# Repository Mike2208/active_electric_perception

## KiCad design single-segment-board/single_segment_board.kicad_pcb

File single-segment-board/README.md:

# single-segment-board

Board for processing single capacitive sensor segment

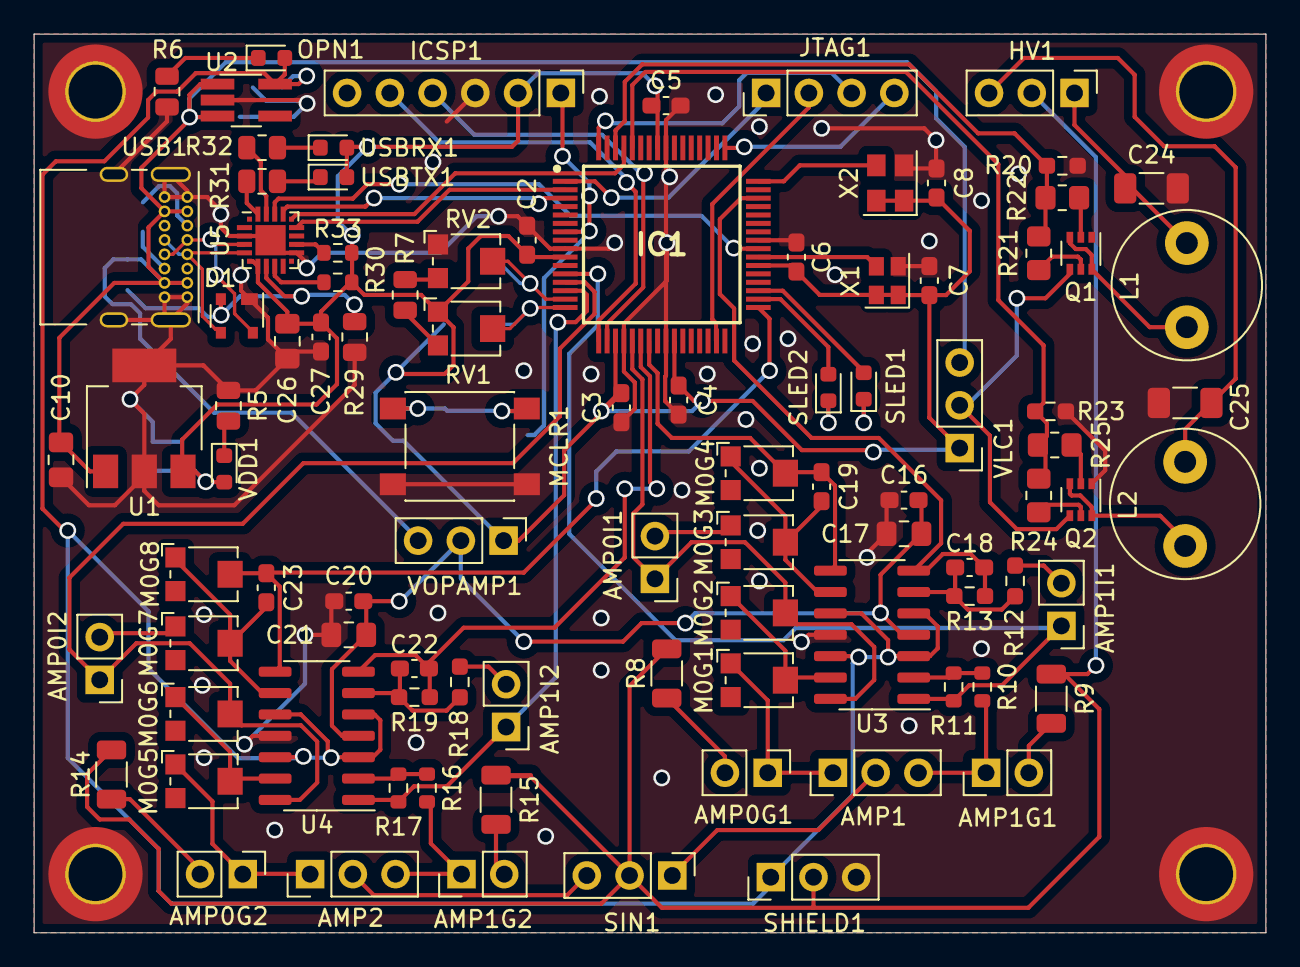
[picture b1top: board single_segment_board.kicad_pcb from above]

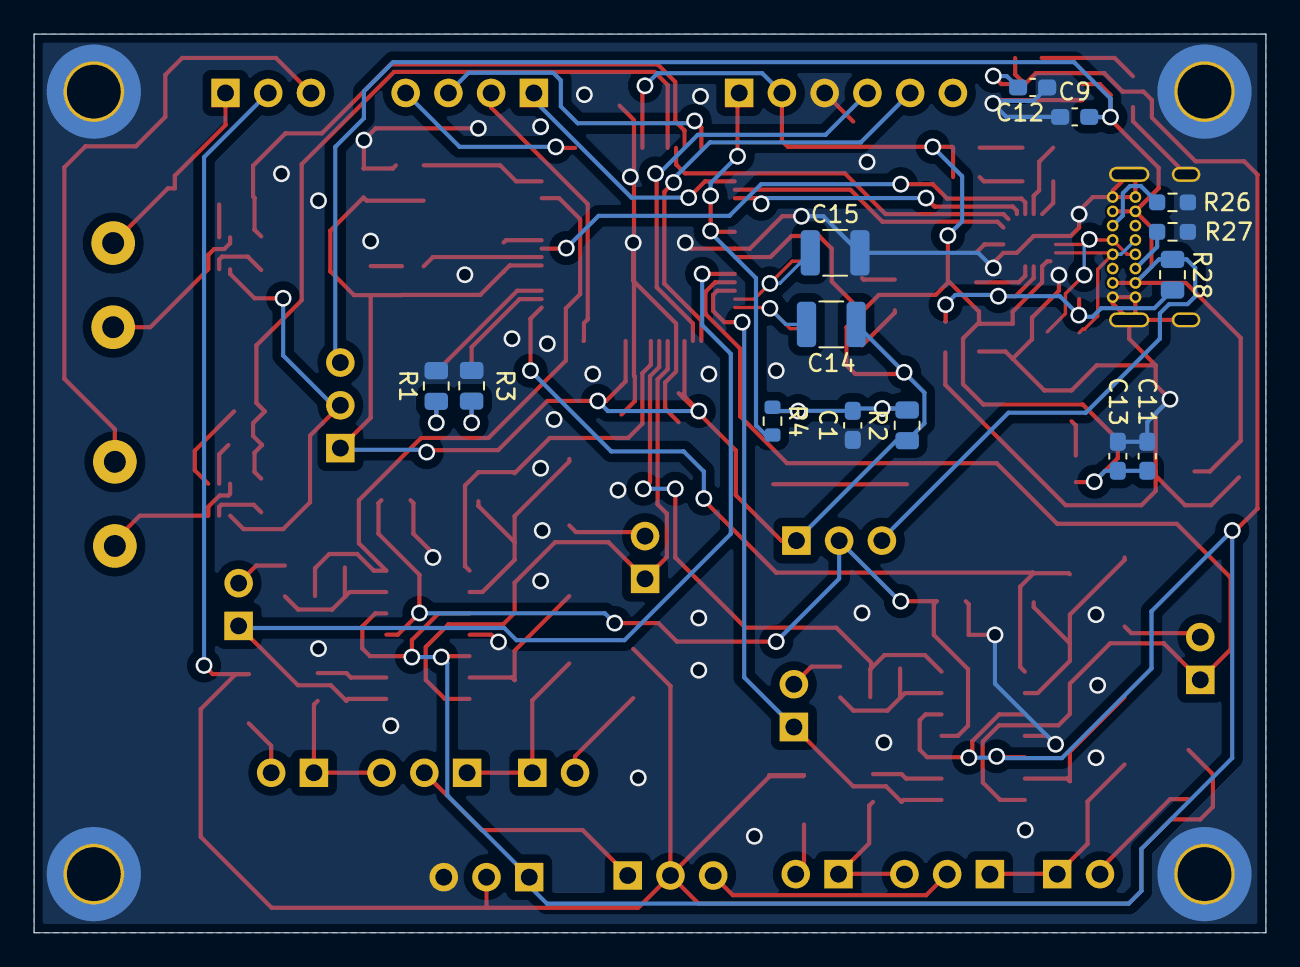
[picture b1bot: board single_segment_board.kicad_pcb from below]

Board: 2 copper layers, 73.2 x 53.4 mm, 112 parts (14 on the bottom side), 82 nets.

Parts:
AMP0G1, AMP0G2, AMP0I1, AMP0I2, AMP1G1, AMP1G2, AMP1I1, AMP1I2: Jumper_2_Open; PinHeader_1x02_P2.54mm_Vertical
AMP1, AMP2: Jumper_3_Bridged12; PinHeader_1x03_P2.54mm_Vertical
C1, C2, C3, C4, C5, C6, C7, C8, C13, C27: 0.1u; C_0603_1608Metric_Pad1.08x0.95mm_HandSolder
C9, C11, C12: 1u; C_0603_1608Metric_Pad1.08x0.95mm_HandSolder
C10, C26: 4.7u; C_0805_2012Metric_Pad1.18x1.45mm_HandSolder
C14, C15: 0.1u; C_1210_3225Metric
C16, C20: .01uF; C_0603_1608Metric_Pad1.08x0.95mm_HandSolder
C17, C21: 10uF; C_0805_2012Metric_Pad1.18x1.45mm_HandSolder
C18, C19, C22, C23: 10p; C_0603_1608Metric_Pad1.08x0.95mm_HandSolder
C24, C25: 47pF; C_1206_3216Metric_Pad1.33x1.80mm_HandSolder
D1: SP0503BAHT; SOT-143
H1, H2, H3, H4: MountingHole_Pad; MountingHole_3.2mm_M3_DIN965_Pad_TopBottom
HV1: Conn_01x03; PinHeader_1x03_P2.54mm_Vertical
IC1: PIC32MK0512MCJ064-I_PT; QFP50P1200X1200X120-64N
ICSP1: ICSP; PinHeader_1x06_P2.54mm_Vertical
JTAG1: JTAG; PinHeader_1x04_P2.54mm_Vertical
L1, L2: 47mH; L_Radial_D8.7mm_P5.00mm_Fastron_07HCP
M0G1, M0G2, M0G3, M0G4, M0G5, M0G6, M0G7, M0G8: RP_500k; Potentiometer_Bourns_TC33X_Vertical
MCLR1: SW_MEC_5E; SW_SPST_PTS645
OPN1: GLED; LED_0603_1608Metric
Q1, Q2: MBT3946DW1T1; SOT-363_SC-70-6
R1, R3, R5, R31, R32: 330; R_0805_2012Metric
R2: 10k; R_0805_2012Metric
R4, R30, R33: 1k; R_0603_1608Metric
R6: 165; R_0805_2012Metric
R7: 150k; R_0805_2012Metric
R8, R9, R14, R15: 1meg; R_1206_3216Metric
R10, R11, R16, R17: 10k; R_0603_1608Metric
R12, R13, R18, R19: 1k; R_0603_1608Metric_Pad0.98x0.95mm_HandSolder
R20, R23: 100k; R_0603_1608Metric_Pad0.98x0.95mm_HandSolder
R21, R22, R24, R25: 10k; R_0805_2012Metric_Pad1.20x1.40mm_HandSolder
R26, R27: 5.1k; R_0603_1608Metric_Pad0.98x0.95mm_HandSolder
R28: 22.1k; R_0805_2012Metric
R29: 47.5k; R_0805_2012Metric
RV1, RV2: RP_50k; Potentiometer_Bourns_TC33X_Vertical
SHIELD1: Jumper_3_Bridged12; PinHeader_1x03_P2.54mm_Vertical
SIN1: Conn_01x03; PinHeader_1x03_P2.54mm_Vertical
SLED1: GLED; LED_0603_1608Metric
SLED2: RLED; LED_0603_1608Metric
U1: MCP1826S; SOT-223-3_TabPin2
U2: NCV8114ASN165T1G; TSOT-23-5_HandSoldering
U3, U4: ADA4891-4; SOIC-14_3.9x8.7mm_P1.27mm
U5: CP2102N-Axx-xQFN20; SiliconLabs_QFN-20-1EP_3x3mm_P0.5mm_EP1.8x1.8mm
USB1: USB_C_Receptacle_USB2.0; USB_C_Receptacle_GCT_USB4085
USBRX1: RLED; LED_0603_1608Metric
USBTX1: GLED; LED_0603_1608Metric
VDD1: GLED; LED_0603_1608Metric
VLC1: Jumper_3_Bridged12; PinHeader_1x03_P2.54mm_Vertical
VOPAMP1: Jumper_3_Bridged12; PinHeader_1x03_P2.54mm_Vertical
X1: SG-210STF; Oscillator_SMD_SeikoEpson_SG210-4Pin_2.5x2.0mm
X2: ECS-327MVATX-3-CN-TR; Oscillator_SMD_Abracon_ASE-4Pin_3.2x2.5mm

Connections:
+3V3: C2.2, C3.1, C4.2, C5.2, C6.1, C7.1, C8.1, C11.1, C13.1, C14.1, C26.1, C27.1, IC1.10 (VDD_1), IC1.19 (AVDD), IC1.26 (VDD_2), IC1.38 (VDD_3), IC1.57 (VDD_4), ICSP1.2, R2.2, R30.2, R33.2, RV1.1, U1.3 (VO), U5.6 (VDD), U5.7 (VREGIN), USBRX1.2 (A), USBTX1.2 (A), VDD1.2 (A), VLC1.1 (A), VOPAMP1.1 (A), X1.1 (~ST), X1.4 (Vcc), X2.1 (VIO), X2.4 (Vcc)
+5V: C9.1, C10.1, R28.1, U1.1 (VI), U2.1 (IN), U2.3 (EN), USB1.A4 (VBUS), USB1.A9 (VBUS), USB1.B4 (VBUS), USB1.B9 (VBUS), VLC1.3 (B), VOPAMP1.3 (B)
/AN0: AMP0I2.1 (A), IC1.13 (OA2OUT/AN0/C2IN4-/C4IN3-/RPA0/RA0), M0G6.2, U4.14
/AN1: AMP1I2.1 (A), IC1.14 (OA2IN+/AN1/C2IN1+/RPA1/RA1), R17.1, U4.1
/AN6: AMP0I1.1 (A), IC1.21 (OA3OUT/AN6/CVD6/C3IN4-/C4IN1+/C4IN4-/RP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), M0G2.2, U3.14
/AN7: C22.2, IC1.22 (OA3IN-/AN7/CVD7/C3IN1-/C4IN1-/RPC1/RC1), R19.2, U4.7
/AN8: C19.2, IC1.23 (OA3IN+/AN8/CVD8/C3IN1+/C3IN3-/RPC2/FLT3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), M0G4.2, U3.8
/AN9: AMP1I1.1 (A), IC1.12 (AN9/CVD9/RPA11/FLT14/RA11), R11.1, U3.1
/AN24: C23.2, IC1.33 (OA5IN+/AN24/CVD24/C5IN1+/C5IN3-/RPA4/RA4), M0G8.2, U4.8
/AN25: C18.2, IC1.46 (OA5OUT/AN25/CVD25/C5IN4-/RPB7/SCK1/INT0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), R13.2, U3.7
/Electrode Connection/HV0: C24.1, HV1.1, L1.2
/Electrode Connection/HV1: C25.1, HV1.3, L2.2
/LC Tanks/PWM0: IC1.62 (RPB12/PWM2H/RB12), R20.1, R21.1, R22.1
/LC Tanks/PWM1: IC1.60 (RPB10/PWM3H/RB10), R23.1, R24.1, R25.1
/LC Tanks/Vlc: Q1.4 (E2), Q2.4 (E2), VLC1.2 (C)
/MCU/MCLR: IC1.7 (MCLR#), ICSP1.1, R4.1
/MCU/PGEC1: IC1.17 (PGC1/OA1IN+/AN4/C1IN1+/C1IN3-/C2IN3-/RP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), ICSP1.5
/MCU/PGED1: IC1.18 (PGD1/OA1IN-/AN5/CTCMP/C1IN1-/RTCC/RPB3/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), ICSP1.4
/MCU/PICU1CTS: IC1.61 (RPB11/PWM3L/RB11), U5.16 (~RTS)
/MCU/PICU1RTS: IC1.2 (RPB14/PWM1H/RB14), U5.15 (~CTS)
/MCU/PICU1RX: IC1.40 (OSCO/CLKO/RPC15/RC15), U5.18 (TXD)
/MCU/PICU1TX: IC1.3 (RPB15/PWM1L/RB15), U5.17 (RXD)
/MCU/RE0: IC1.35 (AN41/CVD41/RPE1/RE1), SLED1.2 (A)
/MCU/RE1: IC1.34 (AN40/CVD40/RPE0/RE0), SLED2.2 (A)
/MCU/TCK: IC1.1 (TCK/RPA7/PWM4L/RA7), JTAG1.1
/MCU/TDI: IC1.31 (TDI/DAC2/AN26/CVD26/RPA8/SDA2/RA8), JTAG1.2
/MCU/TDO: IC1.64 (TDO/PWM4H/RA10), JTAG1.3
/MCU/TMS: IC1.49 (TMS/OA5IN-/AN27/CVD27/LVDIN/C5IN1-/RPB9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), JTAG1.4
/MCU/USB UART Connection/USBD+: D1.4 (K), U5.4 (D+), USB1.A6 (D+), USB1.B6 (D+)
/MCU/USB UART Connection/USBD-: D1.3 (K), U5.5 (D-), USB1.A7 (D-), USB1.B7 (D-)
/Sensor Amplifiers/Sensor Amplifier 01/M0D: AMP1.2 (C), SIN1.1
/Sensor Amplifiers/Sensor Amplifier 01/M0D0: AMP0G1.1 (A), AMP1.1 (A), M0G1.1
/Sensor Amplifiers/Sensor Amplifier 01/M0D1: AMP1.3 (B), AMP1G1.1 (A), R10.2
/Sensor Amplifiers/Sensor Amplifier 02/M0D: AMP2.2 (C), SIN1.3
/Sensor Amplifiers/Sensor Amplifier 02/M0D0: AMP0G2.1 (A), AMP2.1 (A), M0G5.1
/Sensor Amplifiers/Sensor Amplifier 02/M0D1: AMP1G2.1 (A), AMP2.3 (B), R16.2
/Sensor Amplifiers/Vopamp: C16.1, C17.1, C20.1, C21.1, U3.4 (V+), U4.4 (V+), VOPAMP1.2 (C)
/Vref+: C14.2, IC1.16 (PGC3/OA1OUT/VREF+/AN3/C1IN4-/C4IN2-/RPB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), RV1.2
/Vref-: C15.1, IC1.15 (PGD3/VREF-/OA2IN-/AN2/C2IN1-/RPB0/CTED2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), RV2.2
/Vshield: HV1.2, R8.2, R9.2, R14.2, R15.2, SHIELD1.2 (C), SIN1.2
GND: C1.2, C2.1, C3.2, C4.1, C5.1, C6.2, C7.2, C8.2, C9.2, C10.2, C11.2, C12.2, C13.2, C15.2, C16.2, C17.2, C20.2, C21.2, C24.2, C25.2, C26.2, C27.2, D1.1 (A), H1.1, H2.1, H3.1, H4.1, IC1.9 (VSS_1), IC1.20 (AVSS), IC1.25 (VSS_2), IC1.41 (VSS_3), IC1.56 (VSS_4), ICSP1.3, MCLR1.1, MCLR1.2 (1), Q1.1 (E1), Q2.1 (E1), R1.1, R3.1, R5.2, R6.2, R20.2, R23.2, R26.2, R27.2, R29.2, RV2.1, SHIELD1.3 (B), U1.2 (GND), U2.2 (GND), U3.11 (V-), U4.11 (V-), U5.3 (GND), U5.12 (GND), U5.21 (GND), USB1.A1 (GND), USB1.A12 (GND), USB1.B1 (GND), USB1.B12 (GND), USB1.S1 (SHIELD), X1.2 (GND), X2.2 (GND)
NEUT: C12.1, OPN1.2 (A), SHIELD1.1 (A), U2.5 (OUT), U3.3 (+), U3.5 (+), U3.10 (+), U3.12 (+), U4.3 (+), U4.5 (+), U4.10 (+), U4.12 (+)
unnamed: AMP0G1.2 (B), R8.1
unnamed: AMP0G2.2 (B), R14.1
unnamed: AMP0I1.2 (B), M0G3.1
unnamed: AMP0I2.2 (B), M0G7.1
unnamed: AMP1G1.2 (B), R9.1
unnamed: AMP1G2.2 (B), R15.1
unnamed: AMP1I1.2 (B), R12.1
unnamed: AMP1I2.2 (B), R18.1
unnamed: C1.1, MCLR1.3 (K), MCLR1.4 (A), R2.1, R4.2
unnamed: C18.1, R12.2, R13.1, U3.6 (-)
unnamed: C19.1, M0G3.2, M0G4.1, U3.9 (-)
unnamed: C22.1, R18.2, R19.1, U4.6 (-)
unnamed: C23.1, M0G7.2, M0G8.1, U4.9 (-)
unnamed: D1.2 (K), R28.2, R29.1, U5.8 (VBUS)
unnamed: IC1.39 (OSCI/CLKI/AN49/CVD49/RPC12/RC12), X1.3 (OUT)
unnamed: IC1.48 (SOSCO/RPB8/T1CK/RB8), X2.3 (OUT)
unnamed: L1.1, Q1.3 (C2), Q1.6 (C1)
unnamed: L2.1, Q2.3 (C2), Q2.6 (C1)
unnamed: M0G1.2, M0G2.1, U3.13 (-)
unnamed: M0G5.2, M0G6.1, U4.13 (-)
unnamed: OPN1.1 (K), R6.1
unnamed: Q1.2 (B1), R22.2
unnamed: Q1.5 (B2), R21.2
unnamed: Q2.2 (B1), R25.2
unnamed: Q2.5 (B2), R24.2
unnamed: R1.2, SLED1.1 (K)
unnamed: R3.2, SLED2.1 (K)
unnamed: R5.1, VDD1.1 (K)
unnamed: R7.1, RV1.3
unnamed: R7.2, RV2.3
unnamed: R10.1, R11.2, U3.2 (-)
unnamed: R16.1, R17.2, U4.2 (-)
unnamed: R26.1, USB1.A5 (CC1)
unnamed: R27.1, USB1.B5 (CC2)
unnamed: R30.1, U5.9 (~RST)
unnamed: R31.1, U5.20 (~TXT/GPIO.2)
unnamed: R31.2, USBTX1.1 (K)
unnamed: R32.1, USBRX1.1 (K)
unnamed: R32.2, U5.19 (~RXT/GPIO.3)
unnamed: R33.1, U5.13 (~WAKEUP)

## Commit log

2023-03-02 Add files
